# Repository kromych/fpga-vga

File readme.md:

## VGA and FPGAs

The blue, green, red componenets support 4 levels of brightness.

See [Simulations 01](./img/01.png), [Simulations 10](./img/10.png) and [Simulations 11](./img/11.png) 
for the details of the DAC implementation (modeled with [Electronic Circuit Simulator](http://www.falstad.com/circuit/circuitjs.html)).

Here are the TinyFPGA BX and the 4-bit DAC that on the [the breadboard](./img/bb_fpga.jpg) that are connected to a VGA input.
KiCAD schematic and the rendered pdf are under the [kicad](./kicad) directory.

## Installing tools

1. Yosys FPGA toolchain: https://github.com/YosysHQ/fpga-toolchain/releases
2. Tinyprog to program TinyFPGA BX: `pip install tinyprog`

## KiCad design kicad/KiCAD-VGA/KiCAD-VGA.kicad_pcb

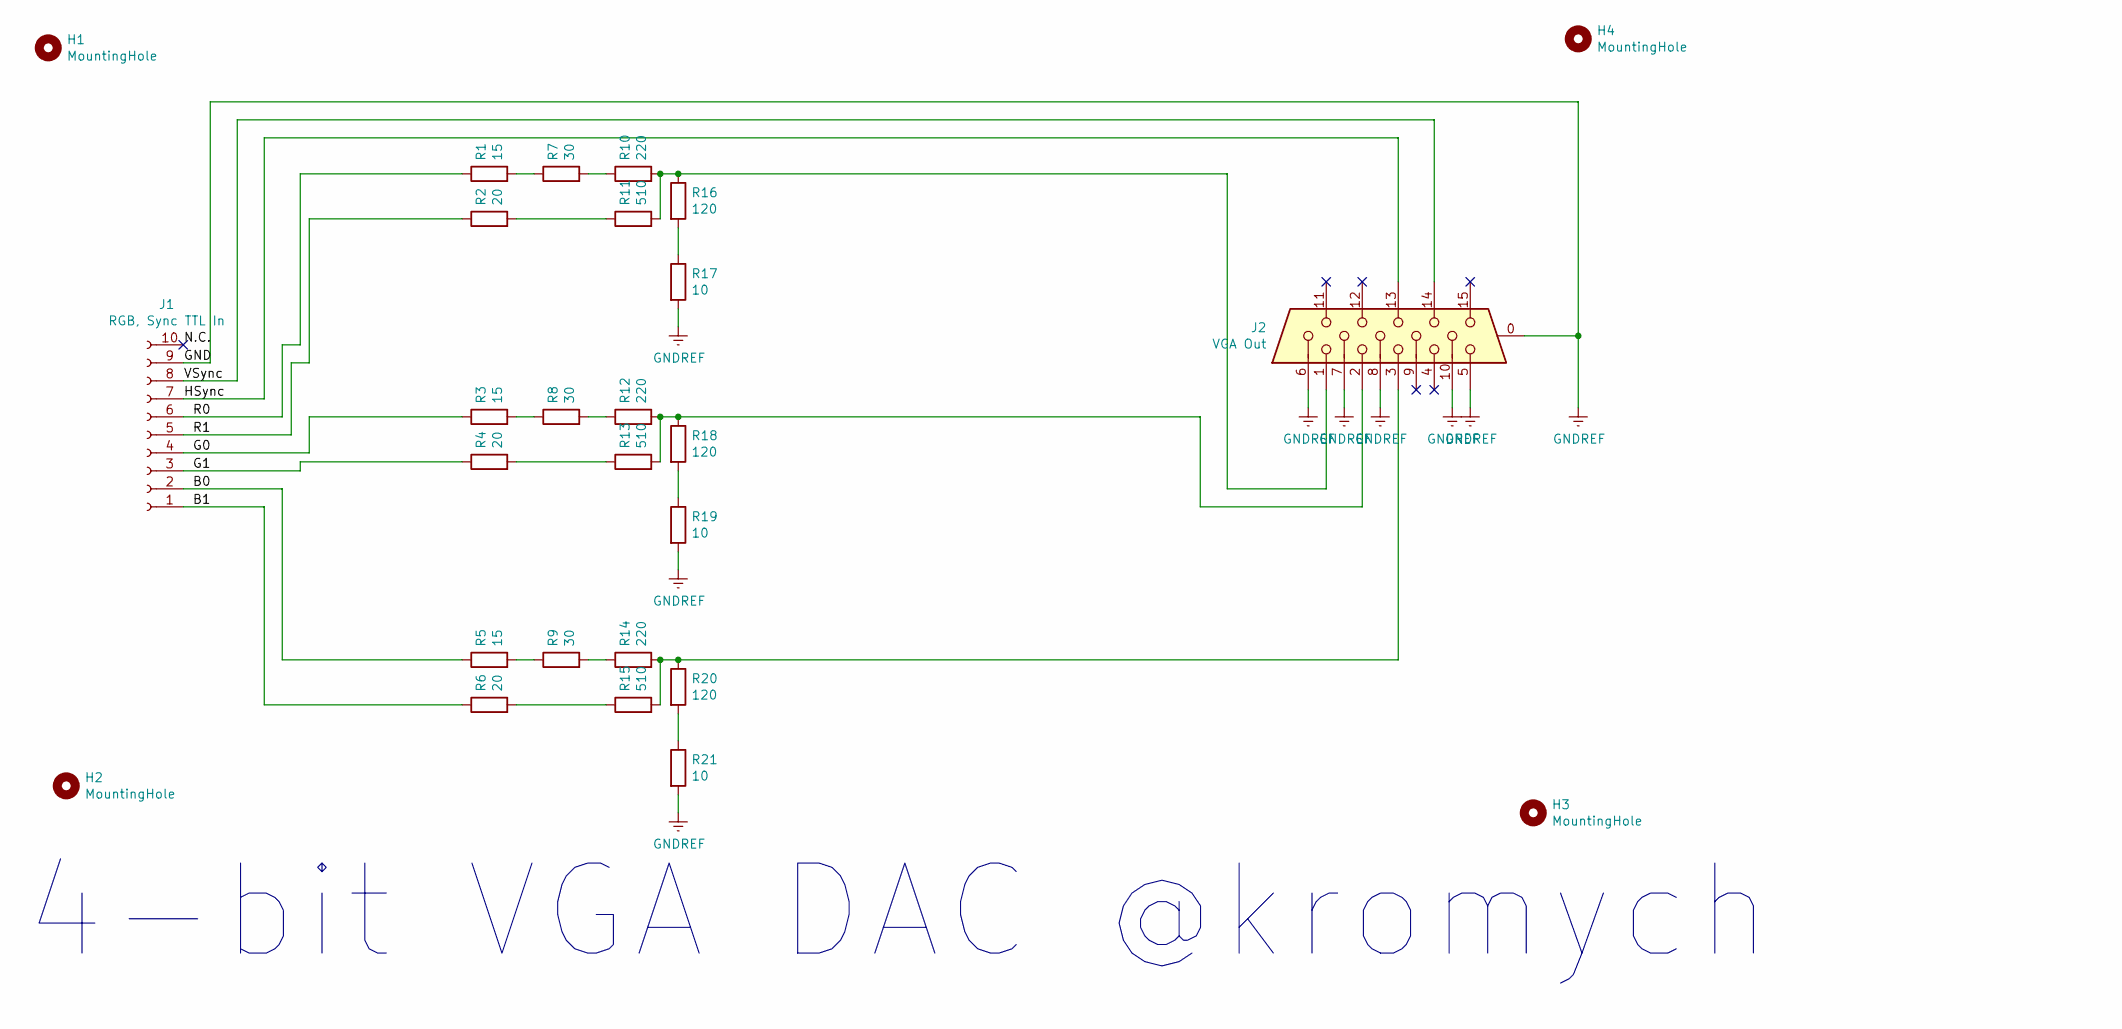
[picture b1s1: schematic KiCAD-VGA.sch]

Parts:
H1, H2, H3, H4: MountingHole; MountingHole_2.2mm_M2_Pad_Via
J1: RGB, Sync TTL In; PinSocket_1x10_P2.54mm_Vertical
J2: VGA Out; DSUB-15-HD_Female_Horizontal_P2.29x1.98mm_EdgePinOffset8.35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
R1, R3, R5: 15; R_Axial_DIN0207_L6.3mm_D2.5mm_P7.62mm_Horizontal
R2, R4, R6: 20; R_Axial_DIN0207_L6.3mm_D2.5mm_P7.62mm_Horizontal
R7, R8, R9: 30; R_Axial_DIN0207_L6.3mm_D2.5mm_P7.62mm_Horizontal
R10, R12, R14: 220; R_Axial_DIN0207_L6.3mm_D2.5mm_P7.62mm_Horizontal
R11, R13, R15: 510; R_Axial_DIN0207_L6.3mm_D2.5mm_P7.62mm_Horizontal
R16, R18, R20: 120; R_Axial_DIN0207_L6.3mm_D2.5mm_P7.62mm_Horizontal
R17, R19, R21: 10; R_Axial_DIN0207_L6.3mm_D2.5mm_P7.62mm_Horizontal

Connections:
/B0: J1.2, R5.1
/B1: J1.1, R6.1
/G0: J1.4, R3.1
/G1: J1.3, R4.1
/HSync: J1.7, J2.13
/R0: J1.6, R1.1
/R1: J1.5, R2.1
/VSync: J1.8, J2.14
GNDREF: J1.9, J2.0, J2.5, J2.6, J2.7, J2.8, J2.10, R17.2, R19.2, R21.2
unnamed: J2.1, R10.2, R11.2, R16.1
unnamed: J2.2, R12.2, R13.2, R18.1
unnamed: J2.3, R14.2, R15.2, R20.1
unnamed: R1.2, R7.1
unnamed: R3.2, R8.1
unnamed: R5.2, R9.1
unnamed: R7.2, R10.1
unnamed: R2.2, R11.1
unnamed: R8.2, R12.1
unnamed: R4.2, R13.1
unnamed: R9.2, R14.1
unnamed: R6.2, R15.1
unnamed: R16.2, R17.1
unnamed: R18.2, R19.1
unnamed: R20.2, R21.1

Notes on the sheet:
4-bit VGA DAC @kromych

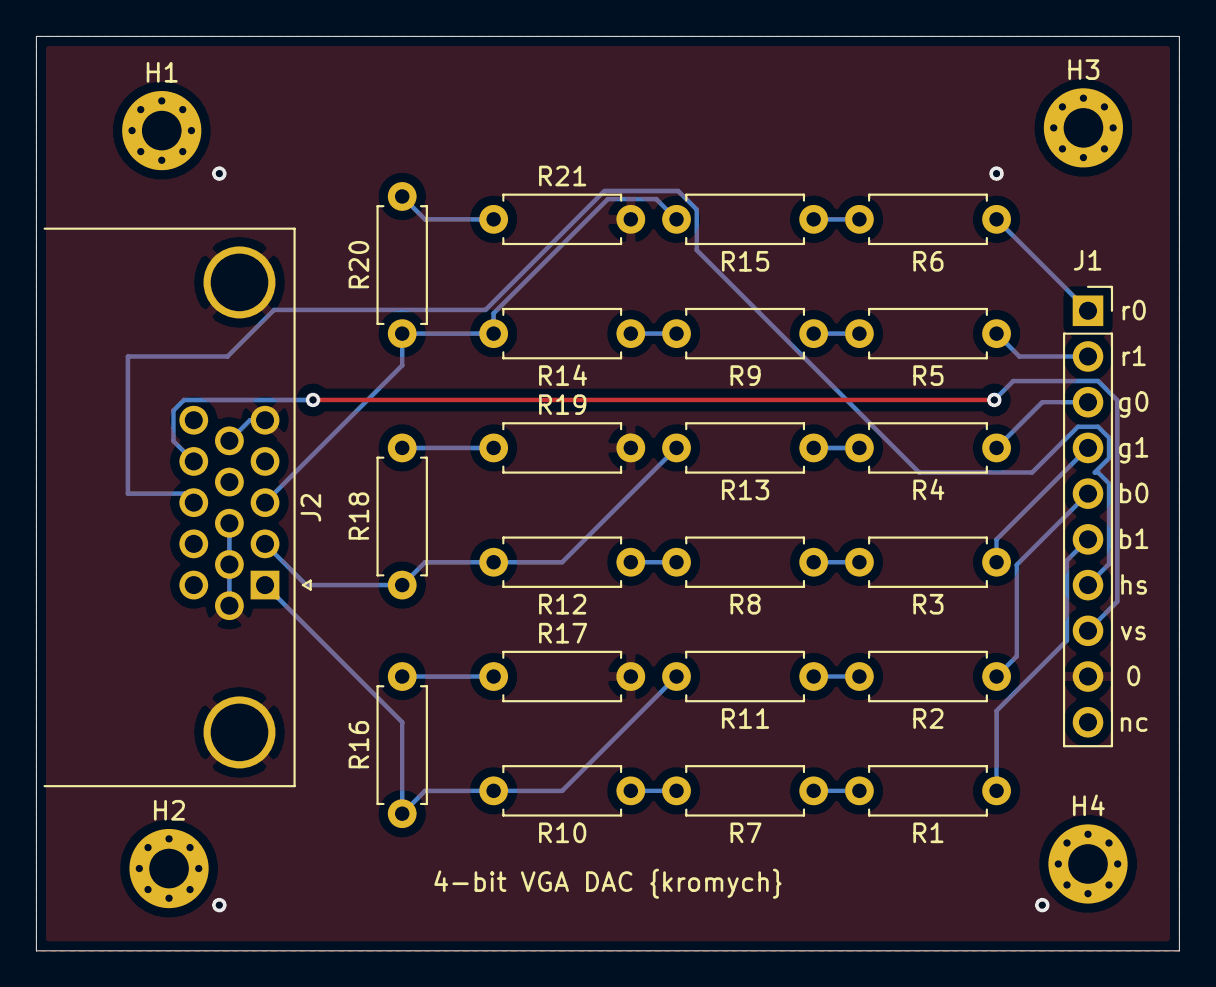
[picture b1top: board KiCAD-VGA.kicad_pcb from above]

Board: 2 copper layers, 63.5 x 50.8 mm, 27 parts (0 on the bottom side), 24 nets.

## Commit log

2020-05-25 Initial drop
2020-05-25 Adjusting timescale in testbed
2020-05-27 Works
2020-05-27 Organize files
2020-05-31 Nicer pattern
2020-05-31 makefile creates output dir
2020-05-31 Digits
2020-06-01 Digits work
2020-09-14 Re-arranging parameters so they are not confused for input files
2020-12-28 KiCAD schematics and the breadboard
2021-01-04 KiCAD project
2021-04-26 Notes on installing tools
2021-04-26 Better pins assignment to match the PCB
2022-04-12 Fix the order of modules
2022-04-18 Port to OrangeCrab
2022-04-18 Port to Orange Crab #2
2022-04-21 Support OrangeCrab only, support 640x480
2022-09-25 Update to OrangeCrab 85F
